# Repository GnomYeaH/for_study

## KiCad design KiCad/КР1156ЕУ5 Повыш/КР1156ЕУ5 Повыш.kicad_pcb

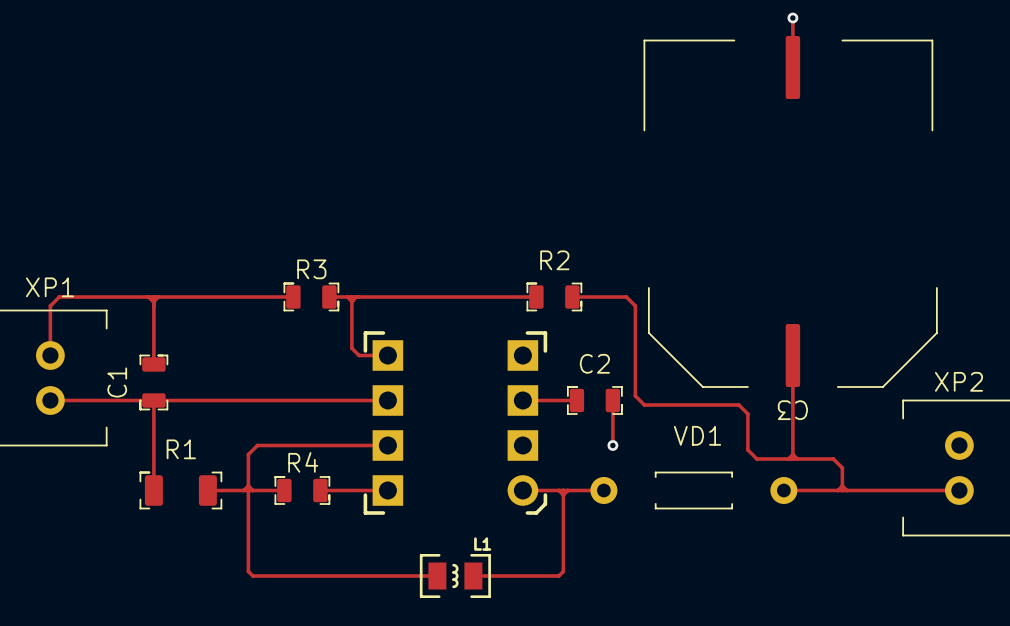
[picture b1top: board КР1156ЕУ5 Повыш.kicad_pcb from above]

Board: 2 copper layers, 12 parts (0 on the bottom side), 8 nets.

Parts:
C1, C2: 1.5мк; 0805
C3: 1.5мк; С_0810
G1: DIP8
L1: Чип_индуктивность*10000н*50В*ВП; Чип-индуктивность_SMD_0805
R1: 1206
R2, R3, R4: 0805
VD1: VD
XP1, XP2: Клеммник наборный

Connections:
GND: C1.2, C2.2, C3.1, G1.2 (E_OUT), G1.4 (GND), R3.1, XP1.2, XP2.2
unnamed: C3.2, R2.2, VD1.2, XP2.1
unnamed: G1.7 (CUR_SENS), L1.1, R1.2, R4.1
unnamed: G1.8 (C_IN), R4.2
unnamed: G1.1 (C_OUT), L1.2, VD1.1
unnamed: C2.1, G1.3 (EXT_CAP)
unnamed: G1.5 (FB), R2.1, R3.2
unnamed: C1.1, G1.6 (VCC(3-40В)), R1.1, XP1.1

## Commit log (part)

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2025-02-25 КП по ОКП
2025-02-25 Ignore example
2025-02-25 Папка ТАУ
    Лаба 1
2025-02-25 mkdir pdf
2025-02-26 Start KP
2025-02-27 подбор двигателя
2025-03-02 Лаба 1 ОТУ
2025-03-03 Много поток в плот
2025-03-03 Начало пиздеца
2025-03-04 Часть ОКП
2025-03-10 ЧмМо для меня и меня и Тимура
2025-03-12 Вариант ЧМО
2025-03-12 Схема кинематическая
2025-03-16 Курсач, изменений много. Впадлу писать о них
2025-03-17 начало моделей компаса
2025-03-17 Курсач, история
2025-03-17 Ворд Маркс
2025-03-19 модели
2025-03-19 диаметр вала
2025-03-19 Диоген
2025-03-19 компас файлы феди
2025-03-19 Изм названия на старое
2025-03-23 ДЗ элеткроника
2025-03-24 исправление эпюр
2025-03-24 Расчет муфты
2025-03-30 Муфта конец
2025-03-31 Муфта 3Д
2025-04-02 Пиздец
    Расчет кинематической погрешности передач редуктора
    Модели для сб
2025-04-06 Сборка без корпуса
2025-04-08 только корпус. чучучучуть мертвый ход
2025-04-08 фото компановки
2025-04-08 Остался сопр переделать
2025-04-13 Корпус 3 части
2025-04-27 дохуя
2025-04-27 xthnt;
2025-05-01 Gnom
2025-05-02 пдф 1
2025-05-13 чмо готово!
2025-05-16 Дохуя, так что похуй
2025-05-20 очень дохуя, такчто похуй
2025-05-26 Тау закрыто, философия
2025-06-15 Рабочие чертежи
2025-06-19 писька-отвалиська
2025-06-23 Повышайка конепц, Курсач усе
2025-09-18 semestr 7
2025-10-05 Лаба 1 по ОТУ
2025-10-10 nx week 6
    week 6
    labs 8
2025-10-17 nx Task 7 AirPlane
2025-10-17 NX Task 9
2025-10-19 Update lab__nonlinear__phase__portraits.zip, отчет 05.10.2025.docx, and 11 more files...
2025-10-24 Week 8
2025-11-06 ТД
    Пиздец ДЗ1
2025-11-07 NX RKT OTU
    10 lab
    RPZ
    2 lab
2025-11-09 NX RKT
    RK2 Example
2025-11-10 NX week 10
2025-11-13 NX
    RK2
2025-11-13 RKT
    предварителлные расчеты
2025-11-16 ГИРДЫ
2025-11-23 nx 12 WEEK
2025-11-29 NX 13
2025-12-04 ОТУ лаба 3, Термопыль ИДЗ2
2025-12-07 Update sem5, RKT KD
2025-12-11 HW_OTU
2025-12-17 Экология, Курсач
    Курсач не правильный (похуй)
2025-12-25 NX end
2025-12-25 NX end end
2026-03-18 ЭСАУ РН и КА отчеты
2026-03-18 add gitignore
2026-04-06 Лабу ЭСАУ, ДЗ БЦВКУ
2026-04-13 Помагити
2026-04-13 Help...
2026-04-13 Имба код
    переписывание и дописавание
2026-04-14 Уря!
    Мб рабочий event 2
    Хз рабочий ли event 3
2026-05-02 Чото
2026-05-16 Обновление
2026-05-16 Деркач БЦВКУ
2026-05-19 ПИЗДЕЦ МНОГО
2026-05-19 Тахоген
2026-05-26 Кайф полнейший
2026-05-27 3D ГПА, Чертежи Егорчика
2026-05-31 Обновление Лаб ЭСАУ
2026-06-21 Гуманитарная помощь Марата
2026-06-22 Чертежи Марата
2026-06-22 Корректировка КД Кадыров
